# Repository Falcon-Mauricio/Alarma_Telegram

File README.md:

# Alarma_Telegram
Repositorio dedicado al desarrollo de una alarma wifi que envia mensajes por "Telegram" cuando el sensor PIR detecta un movimiento

Se trata de un dispositivo de seguridad que utiliza un sensor PIR para vigilar constantemente el área en la que se enfoca. Cuando detecta movimiento, el microcontrolador seleccionado (en este caso, el ESP8266) que está conectado al sensor, envía un mensaje al usuario a través de un BOT de Telegram que le advierte de la activación. Al mismo tiempo, el buzzer se activa intermitentemente para simular una alarma.

Este dispositivo es una solución efectiva para la seguridad en el hogar o en cualquier área en la que se requiera una vigilancia constante. Además, la integración con el BOT de Telegram permite una rápida notificación al usuario en caso de una posible intrusión o actividad sospechosa.

Es importante destacar que, aunque este dispositivo es una medida de seguridad efectiva, no es la única. Es recomendable complementarlo con otras medidas de seguridad, como cerraduras de alta seguridad, iluminación adecuada, y alarmas de seguridad adicionales.
En general, este dispositivo es una solución práctica y de bajo costo para aumentar la seguridad en cualquier área donde se requiera una vigilancia constante.

Archivos Inlcuidos:
- Diseño del Circuito Impreso
- Diseño del Modelo 3D
- Código para la vinculación con Telegram

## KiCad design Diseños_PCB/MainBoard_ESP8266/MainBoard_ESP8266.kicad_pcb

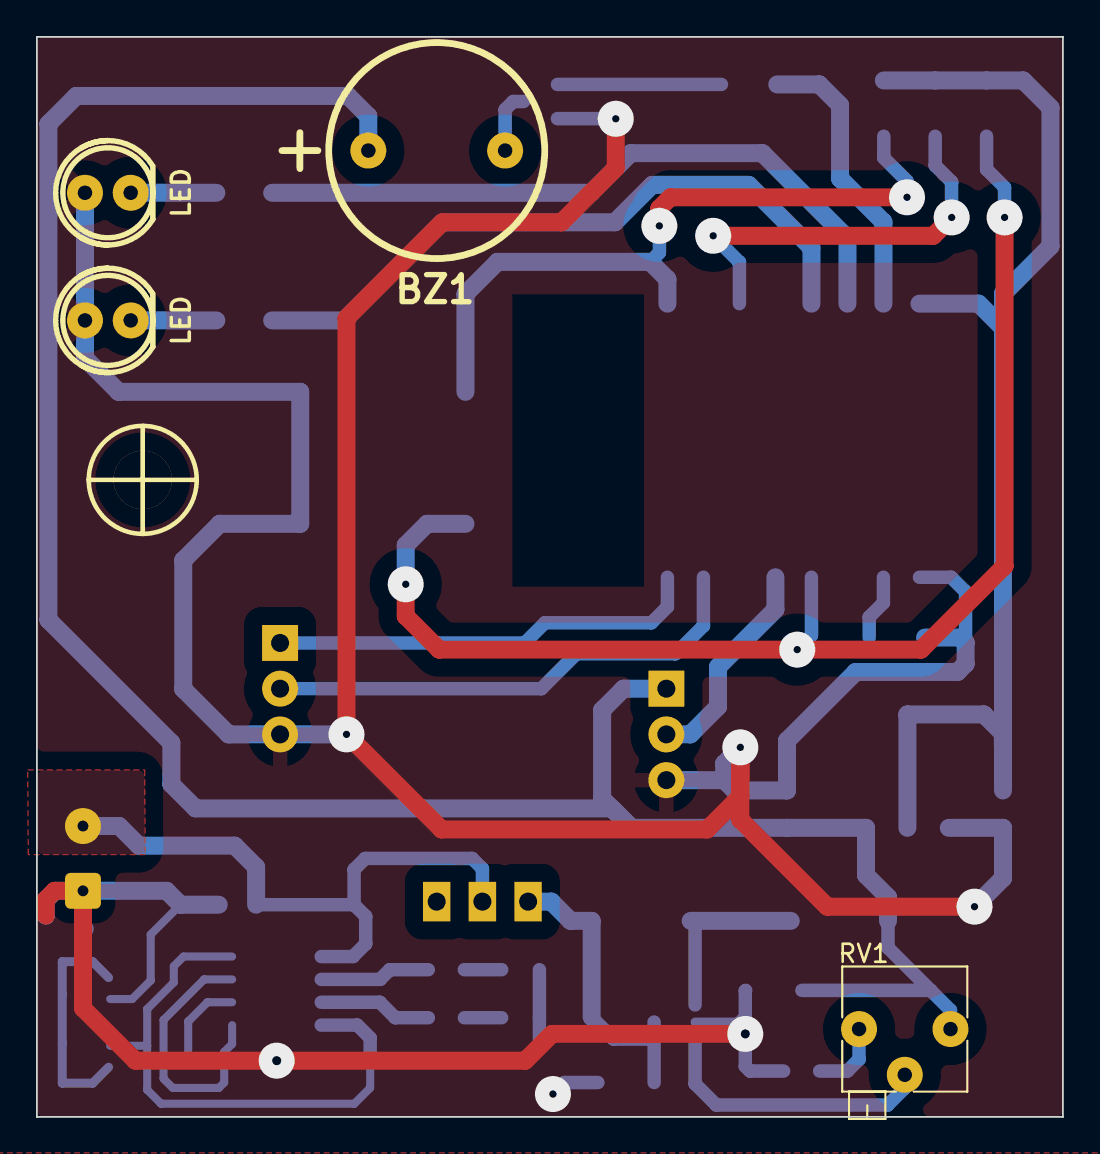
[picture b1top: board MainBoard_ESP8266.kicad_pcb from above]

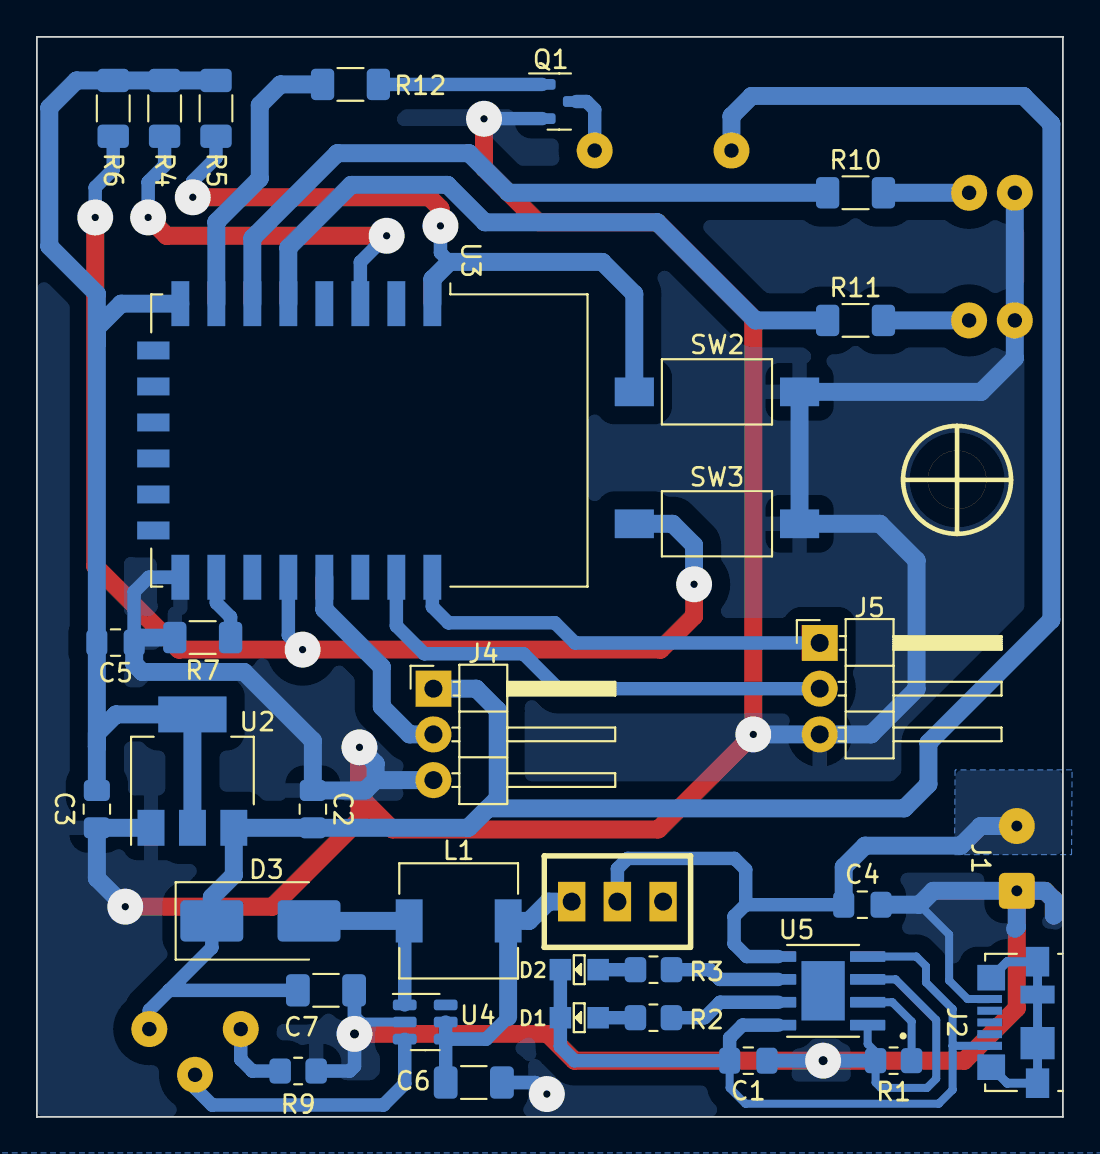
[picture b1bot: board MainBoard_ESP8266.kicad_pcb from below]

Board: 2 copper layers, 57.0 x 60.0 mm, 39 parts (34 on the bottom side), 28 nets.

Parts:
BZ1: Buzzer; Buzzer_12mm
C1, C4, C5: 10uF; C_0805_2012Metric_Pad1.18x1.45mm_HandSolder
C2, C3: 1uF; C_0805_2012Metric_Pad1.18x1.45mm_HandSolder
C6, C7: 22uF; C_1206_3216Metric_Pad1.33x1.80mm_HandSolder
D1, D2: LED; Led_0805
D3: SS34; D_SMB_Handsoldering
D4: LED; led_5mm_red
D5: LED; led_5mm_green
H1: Hole; Separador_M3_5mm
J1: Input_BAT; SolderWire-0.1sqmm_1x02_P3.6mm_D0.4mm_OD1mm
J2: USB_B_Micro; USB_Micro-B_Molex_47346-0001
J4: Sensor; PinHeader_1x03_P2.54mm_Horizontal
J5: FTDI; PinHeader_1x03_P2.54mm_Horizontal
L1: 22uH; L_6.3x6.3_H3
Q1: 2N7002; SOT-23
R1: 1K2; R_0805_2012Metric_Pad1.20x1.40mm_HandSolder
R2, R3: 1K; R_0805_2012Metric_Pad1.20x1.40mm_HandSolder
R4, R5, R6, R7, R12: 10K; R_1206_3216Metric_Pad1.30x1.75mm_HandSolder
R9: 2,2K; R_0805_2012Metric_Pad1.20x1.40mm_HandSolder
R10, R11: 220; R_1206_3216Metric_Pad1.30x1.75mm_HandSolder
RV1: 100K; Potentiometer_Bourns_3266P_Horizontal
SW1: SW_SPDT; SW_SPDT_TH_100Mils_VERTICAL
SW2, SW3: SW_Push; SW_SPST_FSMSM
U2: AMS1117-3.3; SOT-223-3_TabPin2
U3: ESP-12F; ESP-12E
U4: MT3608; SOT-23-6
U5: TP4056; SOP127P600X175-9N

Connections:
+3.3V: C3.1, C5.2, R4.1, R5.1, R6.1, U2.2 (VO), U3.8 (VCC)
+5V: BZ1.1 (-), C2.1, C7.1, D3.1 (A1), J4.1, RV1.3, U2.3 (VI)
/BUZZER: R12.1, U3.7 (GPIO13)
/LED_STATUS: R10.1, U3.6 (GPIO12)
/LED_WIFI: R11.1, U3.5 (GPIO14)
/PIR: J4.2, U3.19 (GPIO4)
/Rx: J5.2, U3.21 (GPIO3/RXD)
/Tx: J5.1, U3.22 (GPIO1/TXD)
/VB: C4.1, J1.2, SW1.2 (B), U5.5 (BAT)
GND: C1.1, C2.2, C3.2, C4.2, C5.1, C6.2, C7.2, D4.1 (K), D5.1 (K), J1.1, J2.5 (GND), J4.3, J5.3, Q1.2 (S), R1.1, R7.2, R9.2, SW2.1, SW3.2, U2.1 (GND), U3.15 (GND), U4.2 (GND), U5.1 (TEMP), U5.3 (GND)
unnamed: BZ1.2 (+), Q1.3 (D)
unnamed: C1.2, D1.2 (A), D2.2 (A), J2.1 (VBUS), U5.4 (VCC), U5.8 (CE)
unnamed: D1.1 (K), R2.2
unnamed: D2.1 (K), R3.2
unnamed: D3.2 (A2), L1.2, U4.1 (SW)
unnamed: D4.2 (A), R10.2
unnamed: D5.2 (A), R11.2
unnamed: Q1.1 (G), R12.2
unnamed: R9.1, RV1.1
unnamed: C6.1, L1.1, SW1.1 (A), U4.4 (EN), U4.5 (IN)
unnamed: R4.2, U3.3 (EN)
unnamed: R6.2, SW3.1, U3.18 (GPIO0)
unnamed: R7.1, U3.16 (GPIO15)
unnamed: R5.2, SW2.2, U3.1 (~RST)
unnamed: RV1.2, U4.3 (FB)
unnamed: R1.2, U5.2 (PROG)
unnamed: R2.1, U5.7 (~CHRG)
unnamed: R3.1, U5.6 (~STDBY)

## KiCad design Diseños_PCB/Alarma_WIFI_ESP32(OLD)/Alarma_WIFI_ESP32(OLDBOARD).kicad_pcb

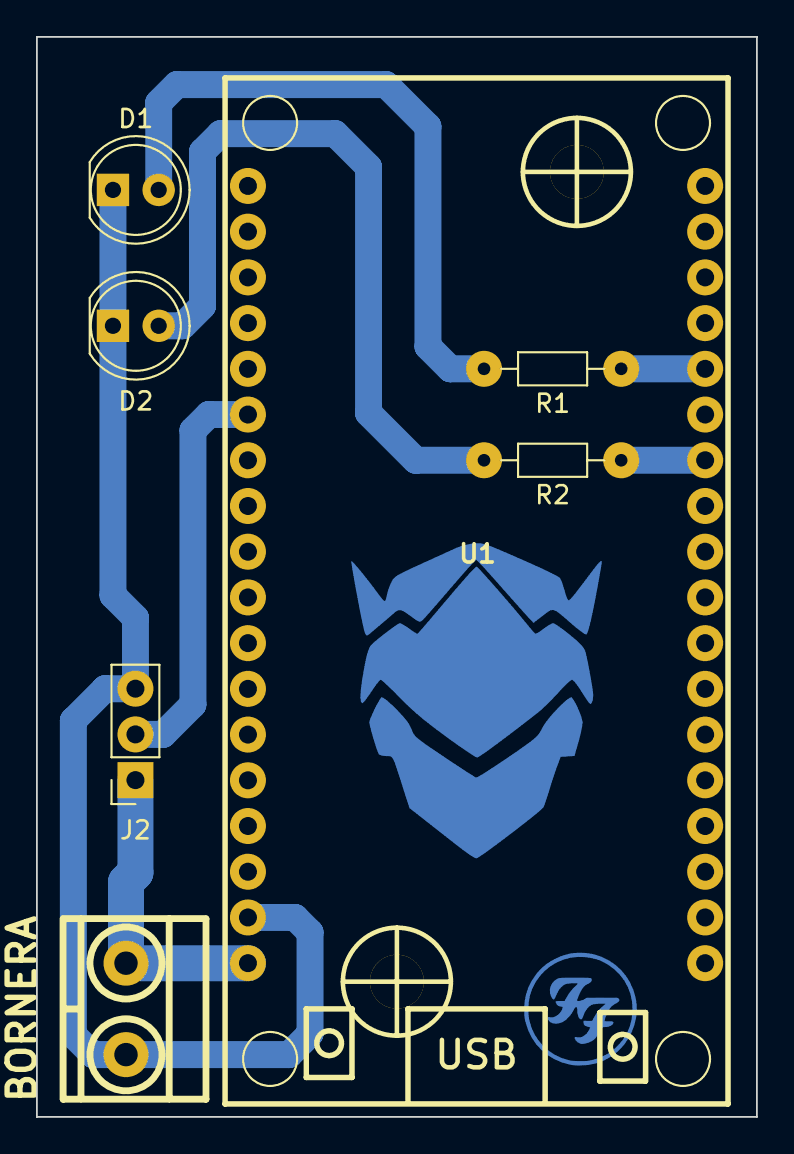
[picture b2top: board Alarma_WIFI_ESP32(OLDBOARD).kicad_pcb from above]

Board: 2 copper layers, 40.0 x 60.0 mm, 9 parts (0 on the bottom side), 7 nets.

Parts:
D1, D2: LED; LED_D5.0mm
H1, H2: MountingHole; hole_3mm
J1: BORNERA; BORNERA2_AZUL
J2: SENSOR PIR; PinSocket_1x03_P2.54mm_Vertical
R1, R2: 330; R_Axial_DIN0204_L3.6mm_D1.6mm_P7.62mm_Horizontal
U1: ESP32_DevKit_V1_DOIT; ESP32_DEVKIT_V1_DOIT

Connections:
+5V: J1.1, J2.1, U1.18 (VIN)
/INPUT_PIR: J2.2, U1.6 (IO32)
/LED_1: R1.1, U1.32 (IO21)
/LED_2: R2.1, U1.30 (IO18)
GND: D1.1 (K), D2.1 (K), J1.2, J2.3, U1.17 (GND)
unnamed: D1.2 (A), R1.2
unnamed: D2.2 (A), R2.2

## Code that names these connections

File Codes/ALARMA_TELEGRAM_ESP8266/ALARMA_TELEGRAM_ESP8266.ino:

#include <ESP8266WiFi.h>
#include <UniversalTelegramBot.h>
#include <ArduinoJson.h>

#define LED_STATUS 12
#define LED_WIFI 14
#define BUZZER 13
#define PIR 4

const char* ssid = "Nombre_de_tu_red";       // Nombre de tu red WiFi
const char* password = "Contraseña_de_tu_red"; // Contraseña de tu red WiFi

// Inicializar BOT Telegram
#define BOTtoken "Token"  // Tu Bot Token (Obtener de Botfather)
// Usa @myidbot para averiguar el chat ID
// Tambien necesita hacer click en "start" antes de  enviarle mensajes el bot
#define CHAT_ID "ID"

WiFiClientSecure client;
UniversalTelegramBot bot(BOTtoken, client);
bool motionDetected = false;

// Indica cuando se detecta movimiento
void IRAM_ATTR detectsMovement() {
  motionDetected = true;
}

void handleNewMessages(int numNewMessages) {

  for (int i = 0; i < numNewMessages; i++) {
    String chat_id = String(bot.messages[i].chat_id);
    if (chat_id != CHAT_ID) {
      bot.sendMessage(chat_id, "Usuario No Autorizado", "");
      continue;
    }

    String text = bot.messages[i].text;

    if (text == "/alarma_on") {
      bot.sendMessage(chat_id, "Alarma activada", "");
      digitalWrite(LED_STATUS, HIGH);
    }

    if (text == "/alarma_off") {
      bot.sendMessage(chat_id, "Alarma desactivada", "");
      digitalWrite(LED_STATUS, LOW);
    }
  }
}

void setup() {
  Serial.begin(115200);
  // Configura el pin PIR como entrada pull-up
  pinMode(PIR, INPUT_PULLUP);
  pinMode(BUZZER, OUTPUT);
  pinMode(LED_WIFI, OUTPUT);
  pinMode(LED_STATUS, OUTPUT);
  digitalWrite(LED_WIFI, LOW);
  for (int i = 0; i < 2; i++) {
      digitalWrite(LED_STATUS, HIGH); // Enciende el LED
      delay(500);
      digitalWrite(LED_STATUS, LOW); // Apaga el LED
      delay(500);
    }
  // Configure el pin PIR como interrupción, asigne la función de interrupción y configure el modo RISING
  attachInterrupt(digitalPinToInterrupt(PIR), detectsMovement, RISING);
  Serial.print("Conectando a la red WiFi: ");
  Serial.println(ssid);
  WiFi.begin(ssid, password);

  while (WiFi.status() != WL_CONNECTED) {
    Serial.print(".");
    digitalWrite(LED_WIFI, LOW);
    delay(500);
  }
  Serial.println("");
  Serial.println("WiFi conectado");
  digitalWrite(LED_WIFI, HIGH);
  Serial.print("Dirección IP asignada: ");
  Serial.println(WiFi.localIP());
  bot.sendMessage(CHAT_ID, "Bot iniciado", "");
}

void loop() {
  int numNewMessages = bot.getUpdates(bot.last_message_received + 1);

  while (numNewMessages) {
    handleNewMessages(numNewMessages);
    numNewMessages = bot.getUpdates(bot.last_message_received + 1);
  }

  if (motionDetected) {
    bot.sendMessage(CHAT_ID, "¡Movimiento detectado!", "");
    for (int i = 0; i < 10; i++) {
      digitalWrite(BUZZER, HIGH); // Enciende el BUZZER
      delay(500);
      digitalWrite(BUZZER, LOW); // Apaga el BUZZER
      delay(500);
    }
    motionDetected = false;
  }
}

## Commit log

2023-05-25 Creacion de los archivos del PCB
2023-05-26 Agregado los archivos del sensor PIR y PCB's
2023-05-27 Edicion archivos pcb
2023-05-27 Diseño del esquematico terminado
2023-05-28 Actualizacion PCB
2023-05-28 Mejoras PCB
2023-05-28 Agregados los archivos viejos de pcbs, creacion del codigo
2023-05-28 Edicion nombre de archivo
2023-05-28 Creacion del codigo funcional para el ESP8266
2023-05-28 Creacion del chasis de la alarma
2023-05-28 Arreglos diseños 3D
